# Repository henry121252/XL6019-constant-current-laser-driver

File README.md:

# XL6019 Constant Current Laser Driver

*V1.3 completed May 17th, 2026*

A modified application of the XL6019, utilizing feedback from a low side shunt resistor for current controlled operation, assembled on a home-etched PCB.

## Specifications

* **Boost converter IC:** XL6019E1 in TO-263-5L
* **Input range:** +5V to +35V
* **Output range:** +5V to +40V
* **Current regulation range:** 50mA to 2.72A

## Architecture

* A low side shunt resistor of value 0.25Ω is installed in series with the standard XL6019 boost circuit. This does mean the output terminal floats at a rate of +0.25V/A, however the converter is intended for driving a laser diode, so this is favorable over a more complex, high side shunt.

* The voltage at the current sense resistor is amplified by a non inverting amplifier with a gain of 6.6, resulting in a voltage of +4.5V at this node when the current is 2.72A. This signal goes into the non inverting input of a differential amplifier. The inverting input is connected to a potentiometer that ranges from 0V to +4.5V. The gain of the amplifier is 33, so if the current sense is just slightly above the target selected by the potentiometer, the op amp drives an MMBT3904 to bring the FB pin of the XL6019 up. This tricks the XL6019 into thinking its voltage is too high and thus lowers the output voltage until the requested current is met, and output voltage of the current sense circuitry equals the 1.25V reference inside the Xl6019. This allows the converter to regulate any positive current from 50mA to 2.75A so long as the load voltage is greater than the input voltage, and the load does not have a negative differential resistance.

* A 5V linear regulator is assembled using the AP431SANTR-G1 as the reference voltage for an MMBT3904 emitter follower from Vin

## Challenges

* This was the first time I had etched PCBs myself, and it was quite difficult getting a working process for manufacturing clean boards. The process involves printing the board's top and bottom masks with a laser printer onto toner transfer paper, then heating it and applying pressure to transfer the mask onto a bare double sided PCB. This board is then immersed in ferric chloride and afterwards the toner mask is wiped away with acetone to reveal a finished PCB. The process allows for rapid prototyping on circuits not suitable for a breadboard such as this one.

* Achieving stable feedback on a device that switches at 180kHz requires a carefully thought out feedback design. The network must be able to react fast enough to changes in the output current while preventing any oscillation in the feedback. A 10nF capacitor from the inverting input of the differential amplifier to its output acts as a low pass filter, lowering amplification of signals above ~482Hz. This drastically reduces the gain of higher frequencies, notably the switching frequency. Without this capacitor it is likely the circuit would oscillate.
   
* The device should be able to regulate voltage with one potentiometer, while seamlessly switching to constant-current regulation with another when the current limit is reached. This creates a natural priority in the signals, as the current regulation takes higher precedence than voltage regulation. This is achieved through a BAS16W diode. When the current sense signal at the emitter of the MMBT3904 is below 1.95V (XL6019 reference voltage + diode drop, the feedback voltage at the XL6019 is equal to the voltage divider feedback. When a current sense signal is present, the feedback voltage is pulled above the 1.25V reference through the diode and MMBT3904.

* To reduce conducted and radiated emissions, hot loops on the converter are minimized heavily. The tight placement of the 100nF decoupling capacitors on the input and output voltage relative to the XL6019 ground provide very low impedance paths to ground for high frequency signals. Larger bulk capacitors are also located nearby to filter lower frequency ripple. These capacitors aid to stabilize the output voltage and reduce interference that could harm other devices.

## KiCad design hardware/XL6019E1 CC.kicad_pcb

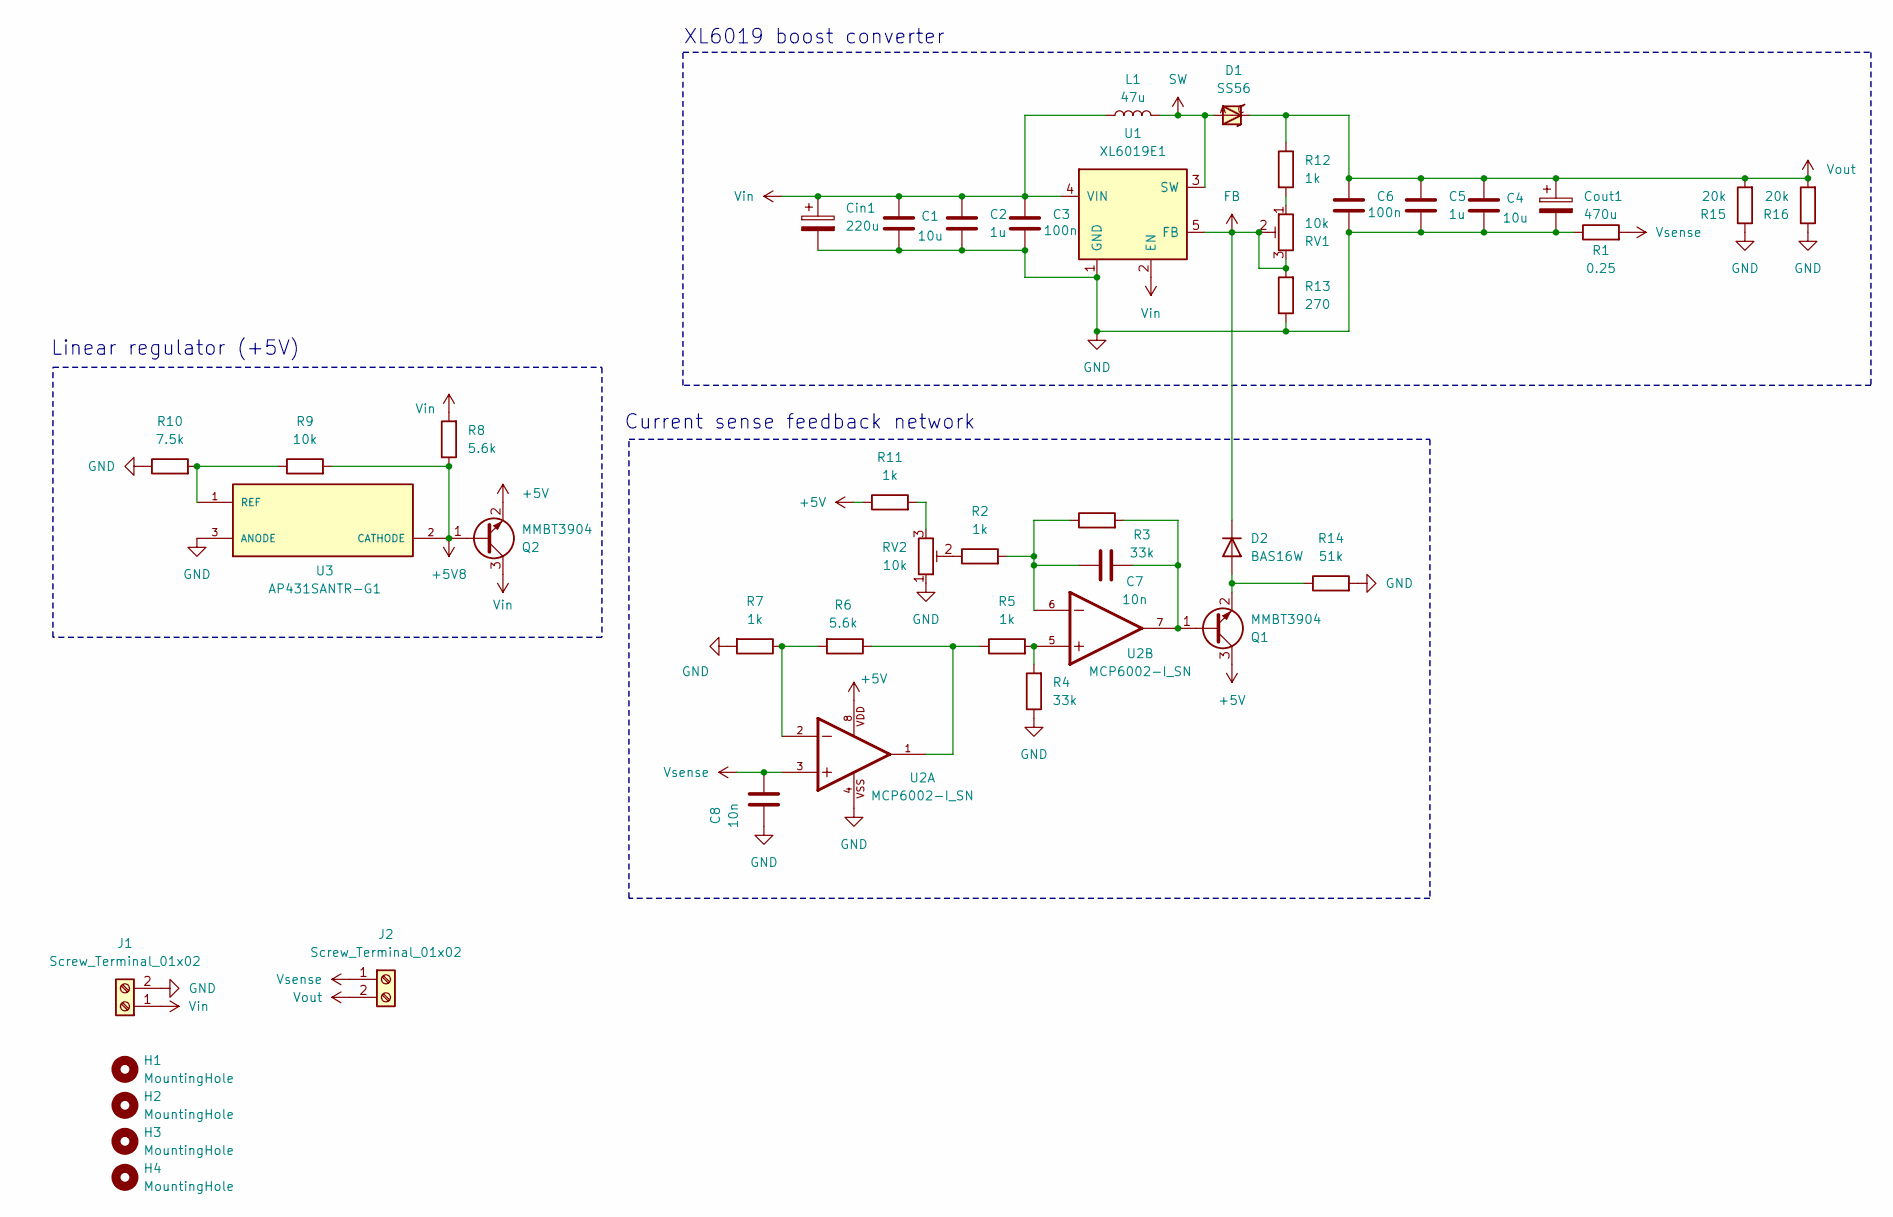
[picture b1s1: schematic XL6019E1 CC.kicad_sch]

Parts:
C1, C4: 10u; C_1206_3216Metric_Pad1.33x1.80mm_HandSolder
C2, C5: 1u; C_0805_2012Metric
C3, C6: 100n; C_0805_2012Metric
C7, C8: 10n; C_0805_2012Metric
Cin1: 220u; CP_Radial_D8.0mm_P3.50mm
Cout1: 470u; CP_Radial_D10.0mm_P5.00mm
D1: SS56; SMB
D2: BAS16W; SOT-323_SC-70
H1, H2, H3, H4: MountingHole; MountingHole_2.2mm_M2_DIN965_Pad
J1, J2: Screw_Terminal_01x02; TerminalBlock_Phoenix_PT-1,5-2-5.0-H_1x02_P5.00mm_Horizontal
L1: 47u; L_Radial_D7.8mm_P5.00mm_Fastron_07HCP
Q1, Q2: MMBT3904; SOT-23
R1: 0.25; R_1210_3225Metric_Pad1.30x2.65mm_HandSolder
R2, R5, R7, R11, R12: 1k; R_1206_3216Metric_Pad1.30x1.75mm_HandSolder
R3, R4: 33k; R_1206_3216Metric_Pad1.30x1.75mm_HandSolder
R6, R8: 5.6k; R_1206_3216Metric_Pad1.30x1.75mm_HandSolder
R9: 10k; R_1206_3216Metric_Pad1.30x1.75mm_HandSolder
R10: 7.5k; R_1206_3216Metric_Pad1.30x1.75mm_HandSolder
R13: 270; R_1206_3216Metric_Pad1.30x1.75mm_HandSolder
R14: 51k; R_1206_3216Metric_Pad1.30x1.75mm_HandSolder
R15, R16: 20k; R_1206_3216Metric_Pad1.30x1.75mm_HandSolder
RV1, RV2: 10k; Potentiometer_Bourns_3224W_Vertical
U1: XL6019E1
U2: MCP6002-I_SN; SOIC127P600X175-8N; PARTREV L
U3: AP431SANTR-G1; VREG_AP431SANTR-G1; PARTREV 1-2

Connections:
+5V: Q1.3 (C), Q2.2 (E), R11.1, U2.8
+5V8: Q2.1 (B), R8.1, R9.2, U3.2 (CATHODE)
FB: D2.3 (K), R13.2, RV1.2, RV1.3, U1.5 (FB)
GND: C1.2, C2.2, C3.2, C4.2, C5.2, C6.2, C8.1, Cin1.2, Cout1.2, J1.2, R1.1, R4.1, R7.2, R10.1, R13.1, R14.2, R15.1, R16.1, RV2.1, U1.1 (GND), U2.4, U3.3 (ANODE)
unnamed: C7.1, R2.2, R3.1, U2.6
unnamed: D2.1 (A), Q1.2 (E), R14.1
unnamed: C7.2, Q1.1 (B), R3.2, U2.7
unnamed: R2.1, RV2.2
unnamed: R4.2, R5.2, U2.5
unnamed: R5.1, R6.1, U2.1
unnamed: R6.2, R7.1, U2.2
unnamed: R11.2, RV2.3
unnamed: R12.2, RV1.1
unnamed: R9.1, R10.2, U3.1 (REF)
SW: D1.A, L1.2, U1.3 (SW)
Vin: C1.1, C2.1, C3.1, Cin1.1, J1.1, L1.1, Q2.3 (C), R8.2, U1.2 (EN), U1.4 (VIN)
Vout: C4.1, C5.1, C6.1, Cout1.1, D1.C, J2.2, R12.1, R15.2, R16.2
Vsense: C8.2, J2.1, R1.2, U2.3

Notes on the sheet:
XL6019 boost converter
Current sense feedback network
Linear regulator (+5V)

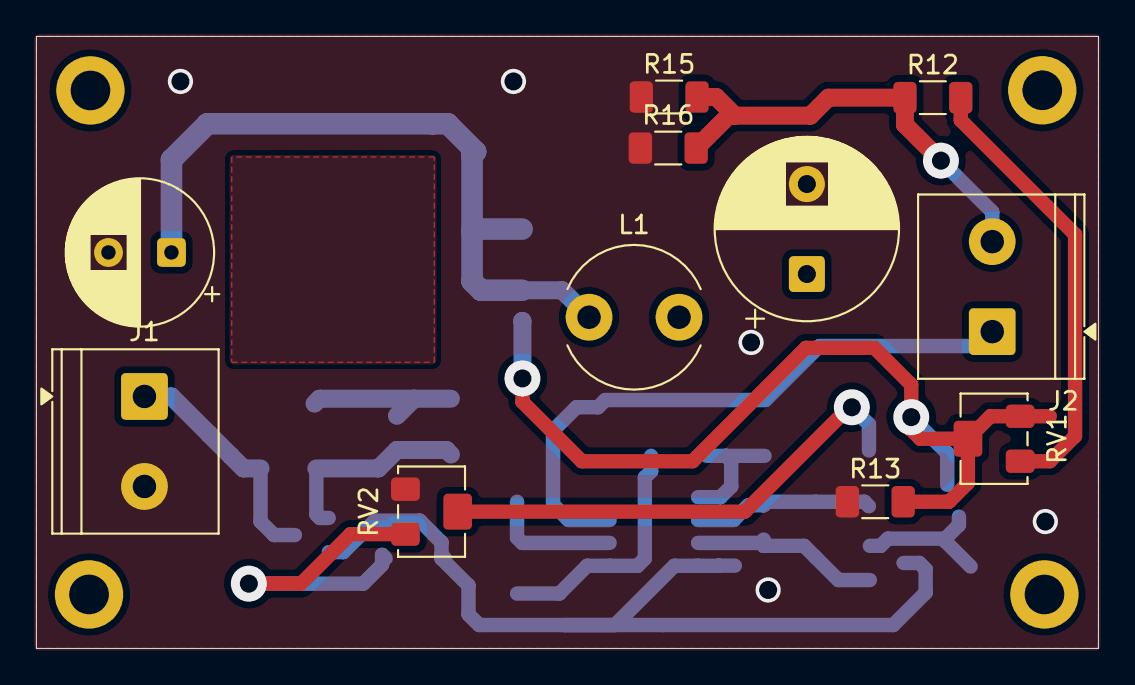
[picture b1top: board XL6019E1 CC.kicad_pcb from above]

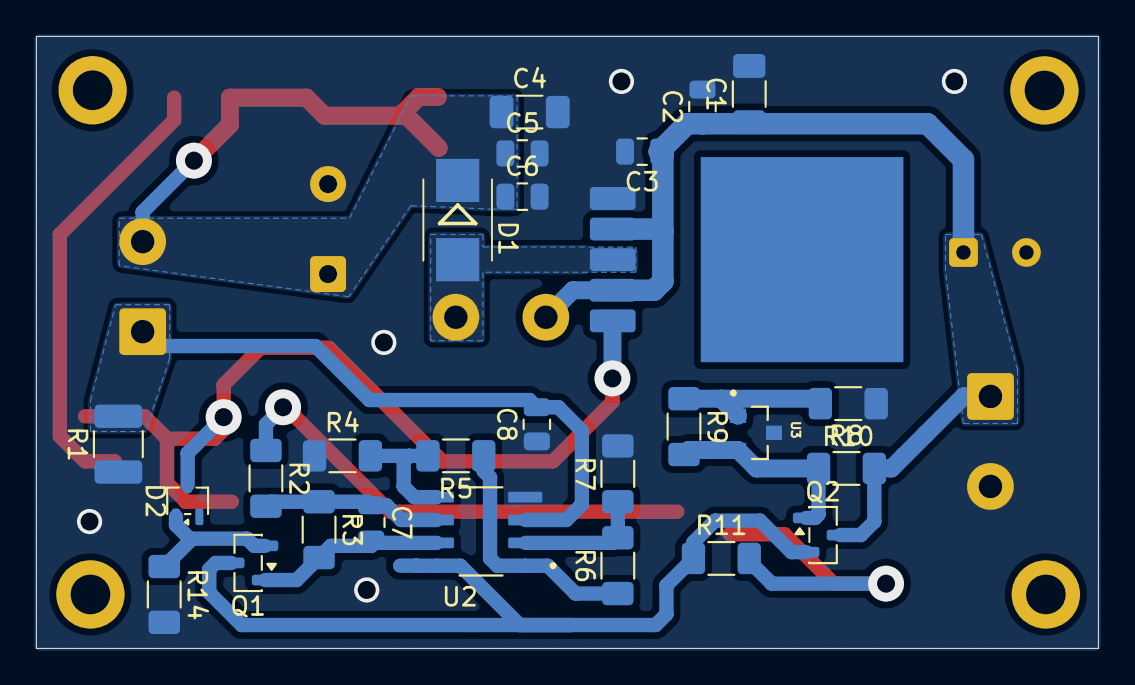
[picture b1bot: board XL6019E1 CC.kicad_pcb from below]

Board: 2 copper layers, 59.0 x 34.0 mm, 42 parts (27 on the bottom side), 18 nets.
